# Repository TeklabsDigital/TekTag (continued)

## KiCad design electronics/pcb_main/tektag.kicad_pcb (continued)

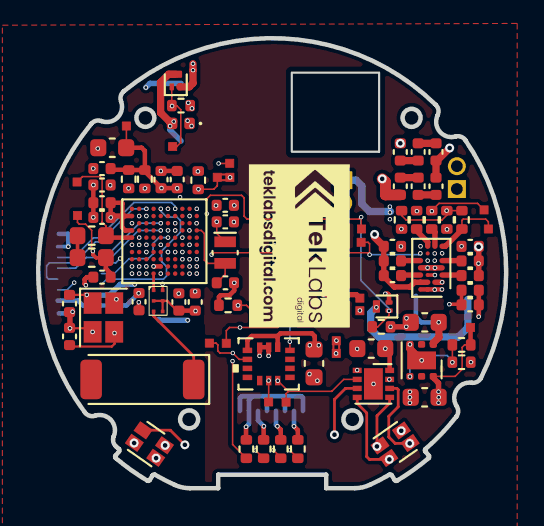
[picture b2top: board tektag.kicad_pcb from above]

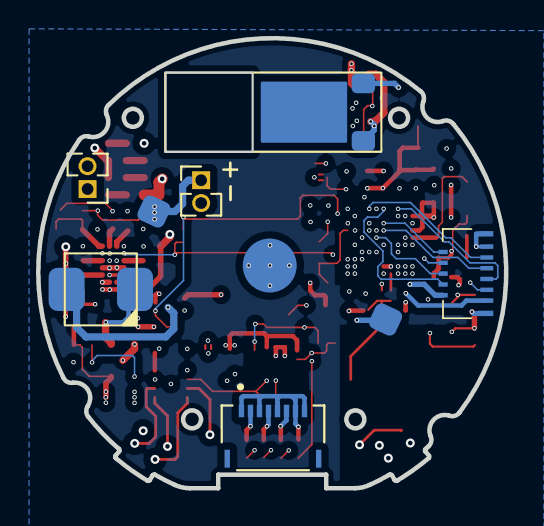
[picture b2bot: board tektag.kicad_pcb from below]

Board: 6 copper layers, 26.0 x 25.0 mm, 92 parts (7 on the bottom side), 66 nets.

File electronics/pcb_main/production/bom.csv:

Designator,Footprint,Quantity,Value,LCSC Part #
AE1,Johanson_2450AT43B100E,1,BLE Antenna,
BOOT0,MicroJump,1,Bridge,
BT1,CP1254 Battery,1,Battery_Cell,
BZ1,Transducer TE044003-4,1,Buzzer,
"C1, C2",0402,2,18pF,
"C10, C11, C12, C13, C14, C15, C7, C8, C9",0402,9,100nF,
"C16, C17, C18",0402,3,C1,
"C19, C20, C21",0402,3,C2,
"C22, C27",0402,2,0.47uF,
"C23, C26",0402,2,22nF,
"C24, C25",0402,2,10nF,
"C28, C29",0402,2,10uF,
"C3, C4",0402,2,12pF,
"C30, C31, C32, C33",0603,4,10uF,
C34,0402,1,1uF,
C35,0402,1,47nF,
C6,0603,1,4.7uF,
D1,LED_LiteOn_LTST-C19HE1WT,1,LEDA,
D2,LED_LiteOn_LTST-C19HE1WT,1,LEDB,
D3,0402,1,1N4148,
J1,Molex 5035661102,1,SWD Trace,
J2,MOLEX_5034800800,1,Touch FFC,
J3,PinHeader_1x02_P1.27mm_Vertical,1,ExtBatt,
JP1,MicroJump-Open,1,5V Trace,
JP2,MicroJump,1,Batt Source,
L1,0603,1,10uH,
L2,0603,1,10nH,
L3,PinHeader_1x02_P1.27mm_Vertical,1,RX Coil,
M1,SMT Motor VZ43FM1B8230001L,1,Motor_DC,
"Q1, Q2",SOT-883,2,2N7002,
"R1, R12, R13, R14, R15, R2",0402,6,1K,
"R10, R11",0402,2,1M,
R16,0402,1,1.5M,
"R3, R8",0402,2,47K,
R4,0402,1,2K4,
R5,0402,1,100K,
R6,0402,1,820R,
R7,0402,1,220R,
R9,0402,1,3.3M,
TH1,0402,1,10k???,
U1,STM32WB55VGY6TR,1,STM32WB55VGY6TR - Seq,
U3,MLPF-WB55-01E3,1,MLPF-WB55-01E3,
U4,Texas_DSBGA-28_1.9x3.0mm_Layout4x7_P0.4mm,1,BQ51052BYFP,
U5,WSON-6-1EP_2x2mm_P0.65mm_EP1x1.6mm,1,TLV75533PDRV,
U6,DFN-8-1EP_2x2mm_P0.5mm_EP1.05x1.75mm,1,KTD2052,
U7,LSM6DSV16XTR,1,LSM6DSV16XTR,
Y1,Crystal_SMD_EuroQuartz_X22-4Pin_2.5x2.0mm,1,32MHz,
Y2,Crystal_SMD_MicroCrystal_CM9V-T1A-2Pin_1.6x1.0mm,1,32768kHz,

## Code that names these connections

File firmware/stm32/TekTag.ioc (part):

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Mcu.Name=STM32WB55VGYx
Mcu.Package=WLCSP100
Mcu.UserName=STM32WB55VGYx
PA0.GPIOParameters=GPIO_Label
PA0.GPIO_Label=MOTOR_EN
PA0.Signal=GPIO_Output
PA1.Signal=GPIO_Output
PA13.Mode=Trace_Synchro_4bits_SW
PA13.Signal=SYS_JTMS-SWDIO
PA14.Mode=Trace_Synchro_4bits_SW
PA14.Signal=SYS_JTCK-SWCLK
PA4.GPIOParameters=GPIO_Label
PA4.GPIO_Label=IMU_INT1
PA4.Signal=GPXTI4
PA5.GPIOParameters=GPIO_Label
PA5.GPIO_Label=IMU_INT2
PA5.Signal=GPXTI5
PB12.GPIOParameters=GPIO_Label
PB12.GPIO_Label=TOUCH_SCAP
PB12.Mode=G1_IO1-Sampling
PB12.Signal=TSC_G1_IO1
PB13.GPIOParameters=GPIO_Label
PB13.GPIO_Label=TOUCH_IO2
PB13.Mode=G1_IO2-Channel
PB13.Signal=TSC_G1_IO2
PB14.GPIOParameters=GPIO_Label
PB14.GPIO_Label=TOUCH_IO3
PB14.Mode=G1_IO3-Channel
PB14.Signal=TSC_G1_IO3
PB15.GPIOParameters=GPIO_Label
PB15.GPIO_Label=TOUCH_IO4G
PB15.Mode=G1_IO4-Channel
PB15.Signal=TSC_G1_IO4
PB4.GPIOParameters=GPIO_Label
PB4.GPIO_Label=TOUCH_G2_SCAP
PB4.Mode=G2_IO1-Sampling
PB4.Signal=TSC_G2_IO1
PB5.GPIOParameters=GPIO_Label
PB5.GPIO_Label=TOUCH_G2_SHIELD
PB5.Mode=G2_IO2-Shield
PB5.Signal=TSC_G2_IO2
PB6.GPIOParameters=GPIO_Speed
PB6.GPIO_Speed=GPIO_SPEED_FREQ_VERY_HIGH
PB6.Mode=I2C
PB6.Signal=I2C1_SCL
PB7.GPIOParameters=GPIO_Speed
PB7.GPIO_Speed=GPIO_SPEED_FREQ_VERY_HIGH
PB7.Mode=I2C
PB7.Signal=I2C1_SDA
PC1.GPIOParameters=GPIO_Label,GPIO_ModeDefaultEXTI
PC1.GPIO_Label=BATT_CHG
PC1.GPIO_ModeDefaultEXTI=GPIO_MODE_IT_FALLING
PC1.Signal=GPXTI1
PC10.Mode=Trace_Synchro_4bits_SW
PC10.Signal=SYS_TRACED1
PC12.Mode=Trace_Synchro_4bits_SW
PC12.Signal=SYS_TRACED3
PC14-OSC32_IN.Mode=LSE-External-Oscillator
PC14-OSC32_IN.Signal=RCC_OSC32_IN
PC15-OSC32_OUT.Mode=LSE-External-Oscillator
PC15-OSC32_OUT.Signal=RCC_OSC32_OUT
PD2.Mode=Trace_Synchro_4bits_SW
PD2.Signal=SYS_TRACED2
PD9.Mode=Trace_Synchro_4bits_SW
PD9.Signal=SYS_TRACED0
PE2.Mode=Trace_Synchro_4bits_SW
PE2.Signal=SYS_TRACECLK
RCC.HSE_VALUE=32000000
RCC.SYSCLKFreq_VALUE=32000000
RCC.SYSCLKSource=RCC_SYSCLKSOURCE_HSE
board=custom

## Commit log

2023-06-12 Create License File
2023-06-12 Added Mechanical Files
2023-06-12 Product Images
2023-06-12 Update LICENSE
2023-06-12 Update to Readme
2023-06-12 PCB Image Update
2023-06-28 BOM update
2023-07-22 Firmware Dev
2023-08-17 Hardware and Firmware udpates
